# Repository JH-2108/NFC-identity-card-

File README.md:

# NFC Identity Card
A custom-designed NFC business card that allows people to instantly access my digital identity and engineering portfolio by tapping their smartphone against the card. 

# Overview 
The NFC identity card is a physical networking card designed to connect to the physical and digital worlds. By integrating an NFC chip and antenna into a custom PCB, the card allows compatible smartphones to access a personal portfolio website without requiring an application or manual URL entry. 

The website serves as a central hub for my identity, engineering projects, technical experience and contact information. 

# How it works
1. A person brings their NFC compatible smartphone close to the card.
2. The smartphone detects the NFC tag.
3. The phone displays a notification or prompt containing the stored URL.
4. The person taps the notification.
5. The person portfolio website opens in their browser.

The card uses passive NFC technology, meaning it does not require a battery or external power sources. 

# Hardware components 
| Component | Purpose | 
|---|---|
| NTAG213 NFC chip | Stores the portfolio URL | 
| Custom PCB NFC antenna | enables wireless NFC communication |
| Custom PCB | Provides the physical card structure | 
| QR code | Provides an alternative way to access the portfolio | 

# Portfolio website 
The website will act as my personal digital identity and engineering portfolio 

Planned sections include: 
- **About me**: Personal introduction and engineering interests.
- **Projects**: A collection of hardware, software and engineering projects.
- **Skills**: Programming languages, electronics, CAD, and technical experience.
- **GitHub**: Links to my repositories and development work.
- **Contact**: Ways to connect with me

# PCB Design
The card will feature a custom PCB layout with an integrated NFC antenna. 

The design will prioritize: 
- Credit-card-sized dimensions.
- Reliable NFC communication.
- Proper antenna layout and tuning
- Durable PCB construction
- Clean and professional visual design.

# Project pictures 

**PCB Design** 

**Front**

**Back**

**Schematics** 

**3D rendered PCB design** 

**Front**

**Back**

**Physical prouct** 

A photo will be added here

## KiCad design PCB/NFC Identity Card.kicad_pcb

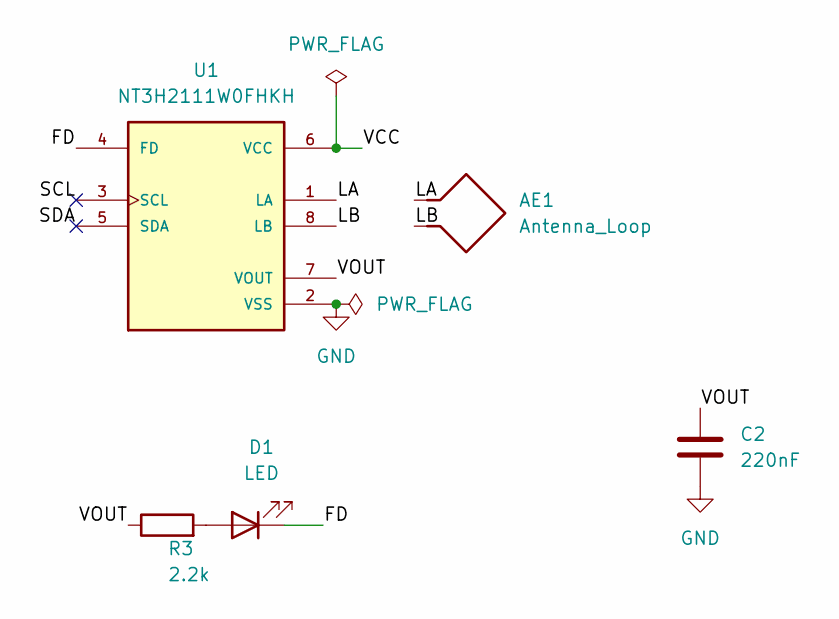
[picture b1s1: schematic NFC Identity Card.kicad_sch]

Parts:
AE1: Antenna_Loop; COIL_GENERATOR regenerated
C2: 220nF; C_0603_1608Metric
D1: LED; LED_0603_1608Metric
R3: 2.2k; R_0603_1608Metric
U1: NT3H2111W0FHKH; QFN8P50_160X160X50L40X20N

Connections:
/FD: D1.1 (K), U1.4 (FD)
/LA: AE1.1, U1.1 (LA)
/LB: AE1.2, U1.8 (LB)
/SCL: U1.3 (SCL)
/SDA: U1.5 (SDA)
/VCC: U1.6 (VCC)
/VOUT: C2.1, R3.1, U1.7 (VOUT)
GND: C2.2, U1.2 (VSS)
unnamed: D1.2 (A), R3.2

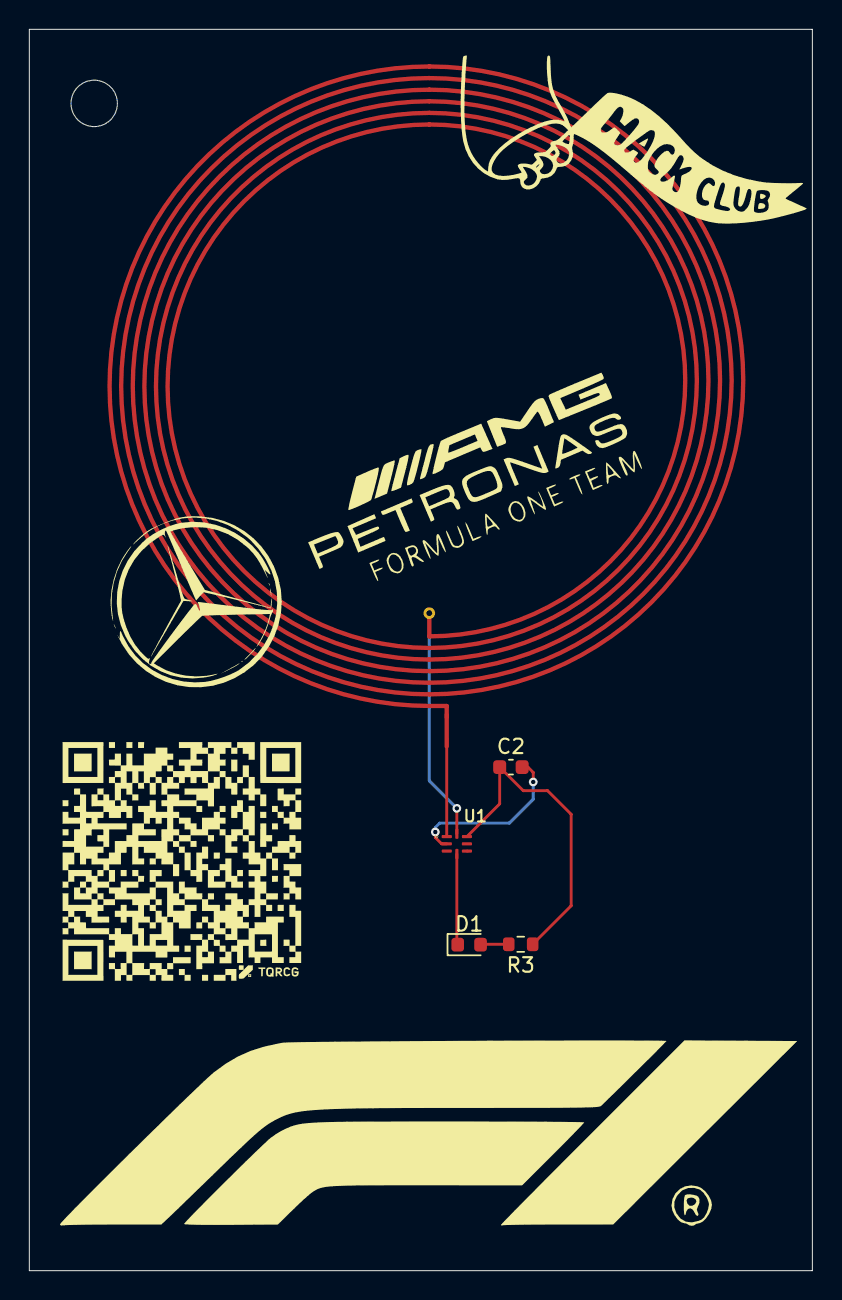
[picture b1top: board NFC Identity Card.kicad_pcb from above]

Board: 2 copper layers, 54.0 x 85.6 mm, 5 parts (0 on the bottom side), 6 nets.
